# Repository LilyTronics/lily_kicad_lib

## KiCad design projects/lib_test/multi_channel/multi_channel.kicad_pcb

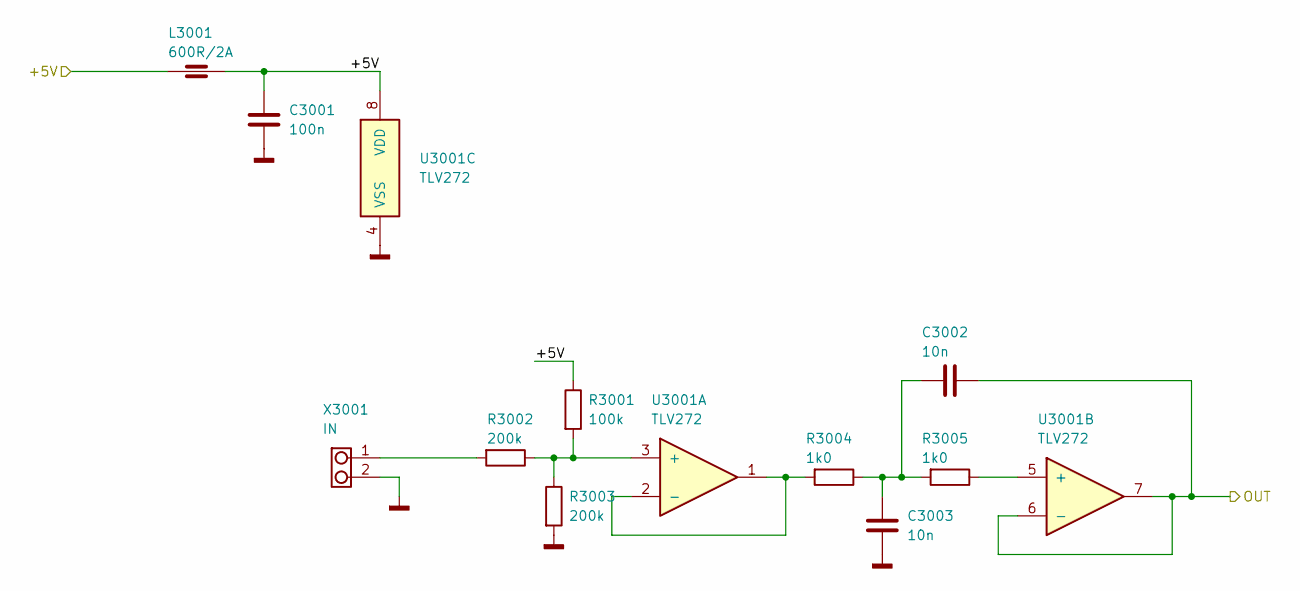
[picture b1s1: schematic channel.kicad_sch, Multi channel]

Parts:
C3001: 100n; cap_0805; JLCPCB_ID C49678
C3002, C3003: 10n; cap_0805; JLCPCB_ID C83170
L3001: 600R/2A; ind_0805; JLCPCB_ID C21519
R3001: 100k; res_0805; JLCPCB_ID C96346
R3002, R3003: 200k; res_0805; JLCPCB_ID C114562
R3004, R3005: 1k0; res_0805; JLCPCB_ID C95781
U3001: TLV272; soic8; JLCPCB_ID C398914
X3001: IN; con_jst_1x02_ph_2.00mm_right_angle_th; JLCPCB_ID C173752

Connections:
/Channel 1/+5V: C3001.1, L3001.1, L3001.2, R3001.1, U3001.8 (VDD); also elsewhere on the board
/Channel 1/OUT: C3002.1, U3001.6 (-), U3001.7; also elsewhere on the board
GND: C3001.2, C3003.2, R3003.2, U3001.4 (VSS), X3001.2; also elsewhere on the board
unnamed: C3002.2, C3003.1, R3004.1, R3005.2
unnamed: R3002.2, X3001.1
unnamed: R3001.2, R3002.1, R3003.1, U3001.3 (+)
unnamed: R3004.2, U3001.1, U3001.2 (-)
unnamed: R3005.1, U3001.5 (+)

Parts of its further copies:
C4001: 100n; cap_0805; JLCPCB_ID C49678
C4002, C4003: 10n; cap_0805; JLCPCB_ID C83170
L4001: 600R/2A; ind_0805; JLCPCB_ID C21519
R4001: 100k; res_0805; JLCPCB_ID C96346
R4002, R4003: 200k; res_0805; JLCPCB_ID C114562
R4004, R4005: 1k0; res_0805; JLCPCB_ID C95781
U4001: TLV272; soic8; JLCPCB_ID C398914
X4001: IN; con_jst_1x02_ph_2.00mm_right_angle_th; JLCPCB_ID C173752

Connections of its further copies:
/Channel 1/+5V: C4001.1, L4001.1, L4001.2, R4001.1, U4001.8 (VDD); also elsewhere on the board
/Channel 2/OUT: C4002.1, U4001.6 (-), U4001.7; also elsewhere on the board
GND: C4001.2, C4003.2, R4003.2, U4001.4 (VSS), X4001.2; also elsewhere on the board
unnamed: C4002.2, C4003.1, R4004.1, R4005.2
unnamed: R4002.2, X4001.1
unnamed: R4001.2, R4002.1, R4003.1, U4001.3 (+)
unnamed: R4004.2, U4001.1, U4001.2 (-)
unnamed: R4005.1, U4001.5 (+)

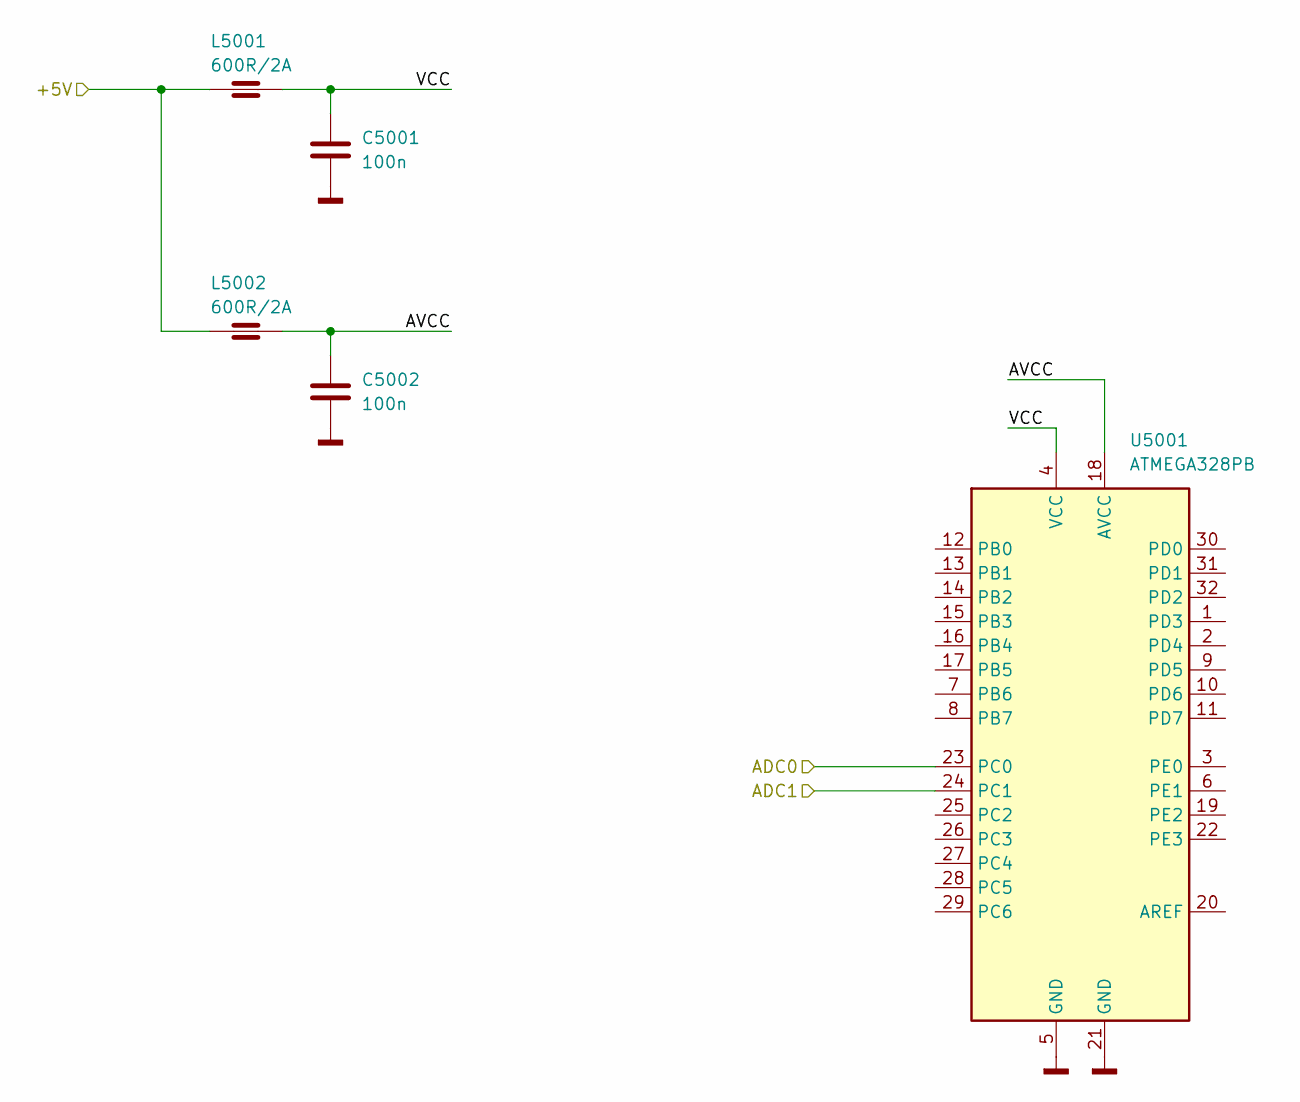
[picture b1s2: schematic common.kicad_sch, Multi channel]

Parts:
C5001, C5002: 100n; cap_0805; JLCPCB_ID C49678
L5001, L5002: 600R/2A; ind_0805; JLCPCB_ID C21519
U5001: ATMEGA328PB; tqfp32_pitch0.8_7x7mm; JLCPCB_ID C132230

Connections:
/Channel 1/+5V: L5001.1, L5002.1; also elsewhere on the board
/Channel 1/OUT: U5001.23 (PC0); also elsewhere on the board
/Channel 2/OUT: U5001.24 (PC1); also elsewhere on the board
/Common/AVCC: C5002.1, L5002.2, U5001.18 (AVCC)
/Common/VCC: C5001.1, L5001.2, U5001.4 (VCC)
GND: C5001.2, C5002.2, U5001.5 (GND), U5001.21 (GND); also elsewhere on the board

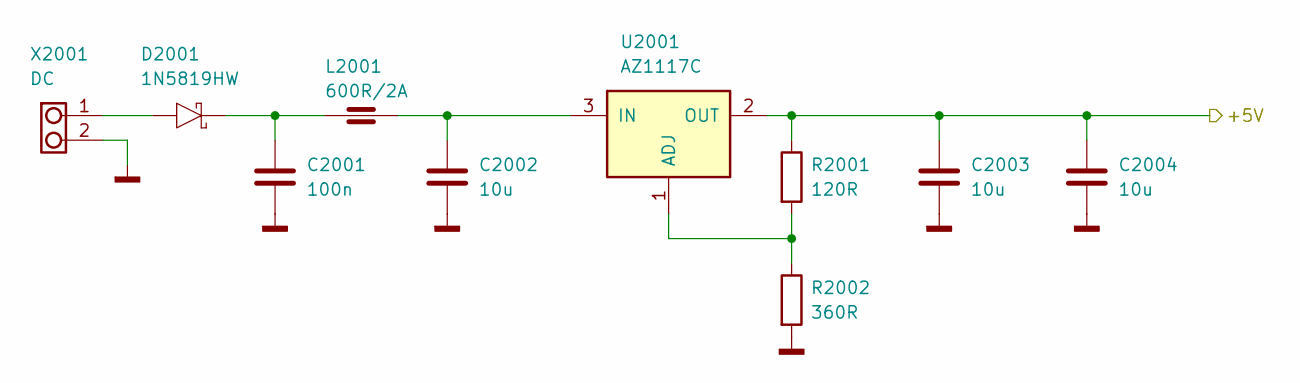
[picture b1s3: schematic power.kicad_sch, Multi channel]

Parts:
C2001: 100n; cap_0805; JLCPCB_ID C49678
C2002, C2003, C2004: 10u; cap_0805; JLCPCB_ID C15850
D2001: 1N5819HW; dio_sod123; JLCPCB_ID C82544
L2001: 600R/2A; ind_0805; JLCPCB_ID C21519
R2001: 120R; res_0805; JLCPCB_ID C114245
R2002: 360R; res_0805; JLCPCB_ID C137538
U2001: AZ1117C; sot223; JLCPCB_ID C95398
X2001: DC; con_jst_1x02_vh_3.96mm_right_angle_th; JLCPCB_ID C158007

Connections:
/Channel 1/+5V: C2003.1, C2004.1, R2001.1, U2001.2 (OUT); also elsewhere on the board
GND: C2001.2, C2002.2, C2003.2, C2004.2, R2002.2, X2001.2; also elsewhere on the board
unnamed: C2001.1, D2001.1, L2001.1
unnamed: D2001.2, X2001.1
unnamed: R2001.2, R2002.1, U2001.1 (ADJ)
unnamed: C2002.1, L2001.2, U2001.3 (IN)

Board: 2 copper layers, 37 parts (0 on the bottom side), 20 nets, no tracks yet.
